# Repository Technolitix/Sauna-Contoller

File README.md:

# Sauna Controller

A project for controlling a sauna using sensors and actuators. This application allows precise management of temperature, humidity, and other parameters to ensure an optimal sauna experience.

---

## Features

- **Temperature Control**: Automatically adjusts the temperature based on predefined settings.
- **Humidity Management**: Integrates humidity sensors for maintaining the perfect sauna environment.
- **Scheduling**: Enables the sauna to operate at predefined times.
- **Fallback Mode**: Ensures stable operation even during connectivity issues.

---

## Configuration Overview

The main configuration file is `sauna1.yaml`. It contains all the necessary settings for operating the sauna controller. Sensitive data such as passwords and API keys are managed through references (`!secret`) in a separate file, such as `secrets.yaml`.

Example of a reference in the YAML file:
```yaml
wifi:
  ssid: !secret wifi_ssid_sauna
  password: !secret wifi_password_sauna
```

### Note
The `secrets.yaml` file is not included in this repository. It should contain sensitive data and remain private.

---

## Directory Structure

- **`config/`**: Contains main configuration files like `sauna1.yaml`.
- **`pictures/`**: Contains images for documentation and illustration.
- **`scripts/`**: Scripts supporting sauna control.
- **`logs/`**: Log files for debugging and tracking.

---

## Installation and Usage

### Prerequisites

- A device capable of managing the controller (e.g., Raspberry Pi, ESP32).
- Sensors and actuators compatible with the sauna setup.

### Steps

1. **Clone the repository**:
   ```bash
   git clone https://github.com/Technolitix/Sauna-Controller.git
   ```
2. **Adjust the configuration file**:
   Edit `sauna1.yaml` to suit your sauna's specific requirements.
3. **Configure secrets**:
   Create a `secrets.yaml` file and add sensitive data:
   ```yaml
   wifi_ssid_sauna: "YourWiFiName"
   wifi_password_sauna: "YourWiFiPassword"
   ```
4. **Deploy and start**:
   Upload the configuration to your device and start the controller.

---

## Security

- The `secrets.yaml` file should never be included in the repository.
- Always ensure sensitive data is stored externally and securely.

---

## Contact

If you have any questions or issues, feel free to open an [Issue](https://github.com/Technolitix/Sauna-Controller/issues).

---

## License

This project is licensed under the [MIT License](LICENSE).

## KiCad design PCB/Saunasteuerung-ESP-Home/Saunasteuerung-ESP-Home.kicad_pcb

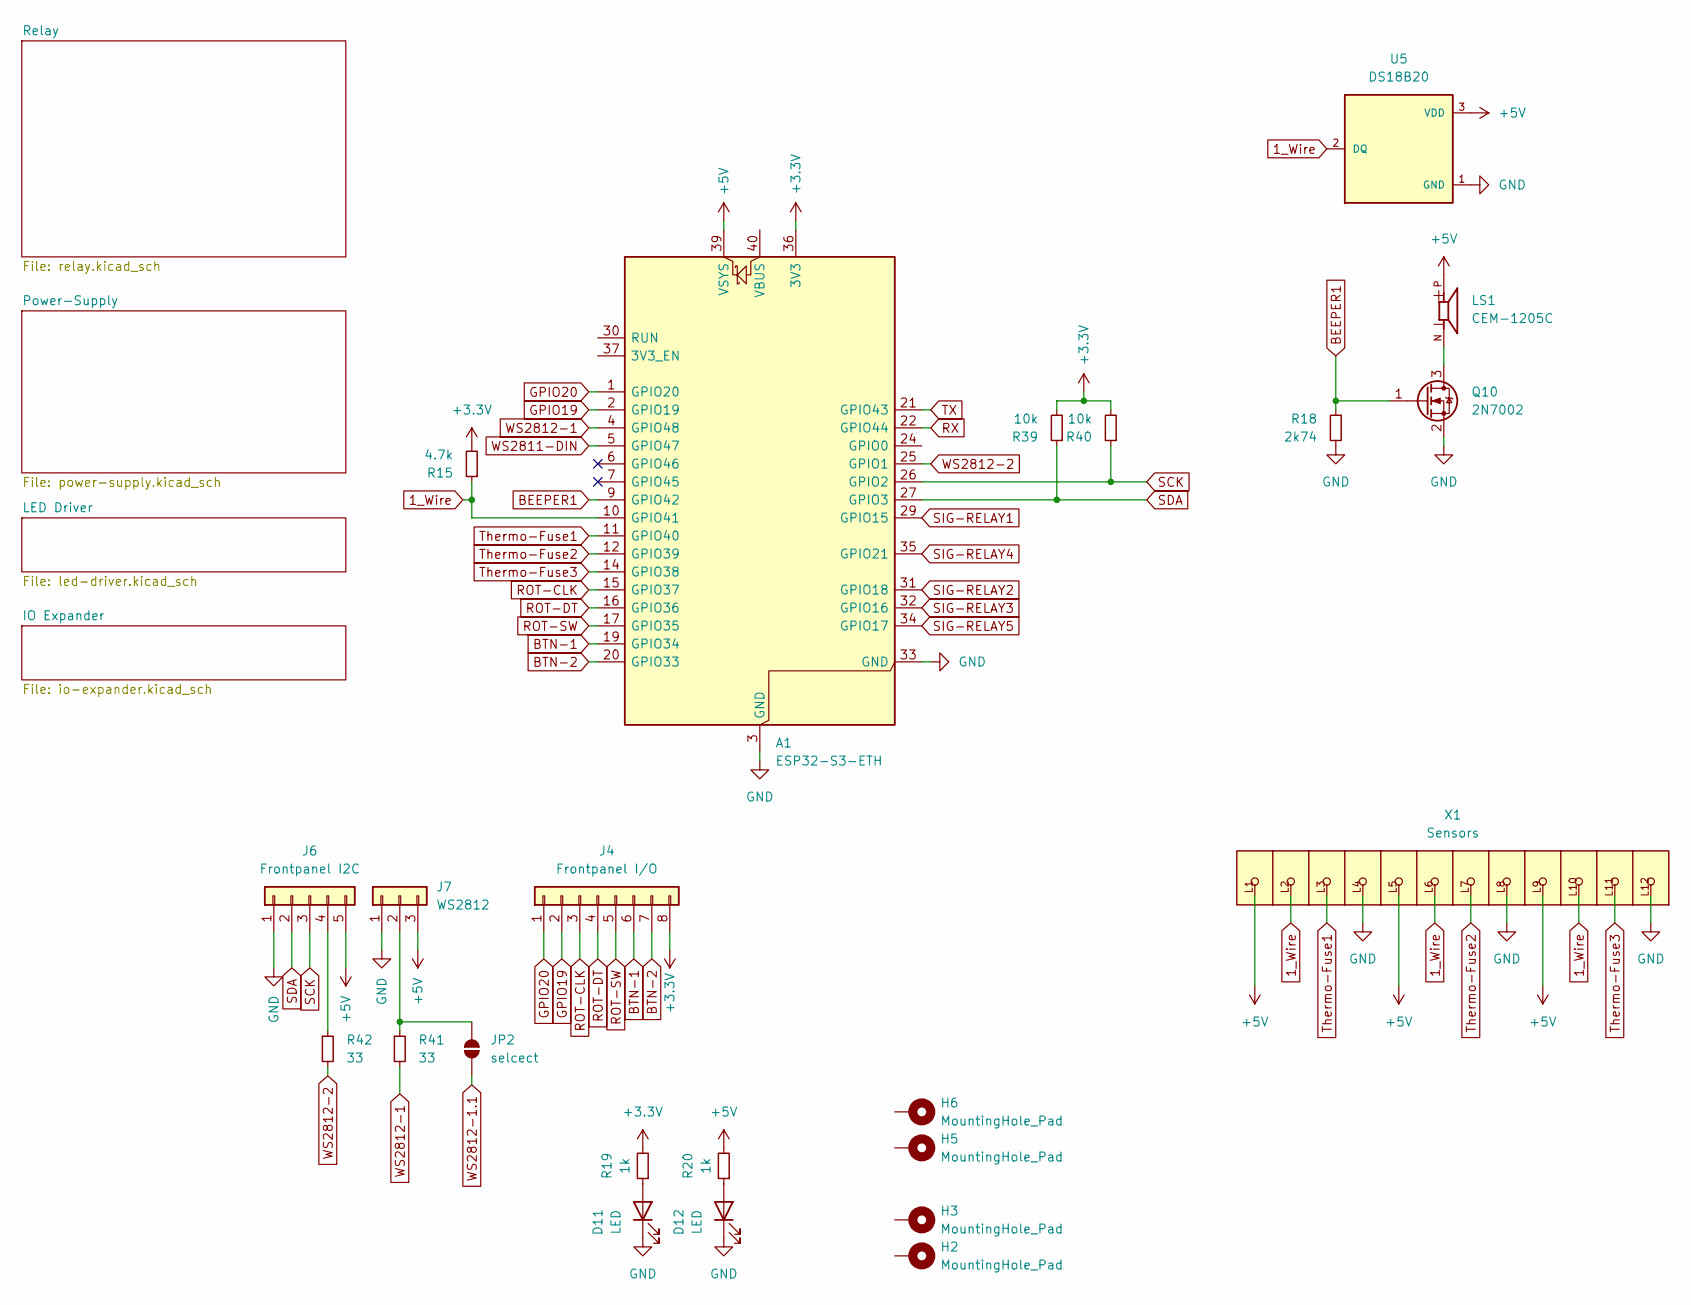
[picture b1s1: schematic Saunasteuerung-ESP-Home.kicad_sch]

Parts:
A1: ESP32-S3-ETH
D11, D12: LED; LED_0603_1608Metric
H2, H3, H5, H6: MountingHole_Pad; MountingHole_3.2mm_M3_DIN965_Pad_TopBottom
J4: Frontpanel I/O; JST_XH_B8B-XH-A_1x08_P2.50mm_Vertical
J6: Frontpanel I2C; JST_XH_B5B-XH-A_1x05_P2.50mm_Vertical
J7: WS2812; JST_XH_B3B-XH-A_1x03_P2.50mm_Vertical
JP2: selcect; SolderJumper-2_P1.3mm_Open_TrianglePad1.0x1.5mm
LS1: CEM-1205C; CEM-1205C_CUI_CEM-1205C
Q10: 2N7002; SOT-23
R15: 4.7k; R_0603_1608Metric
R18: 2k74; R_0603_1608Metric
R19, R20: 1k; R_0603_1608Metric
R39, R40: 10k; R_0603_1608Metric
R41, R42: 33; R_0603_1608Metric
U5: DS18B20; TO-92L; PARTREV 5
X1: Sensors; 250-212_P-250-212

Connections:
1_Wire: A1.10 (GPIO41), R15.1, U5.2 (DQ), X1.L2, X1.L6, X1.L10
+3.3V: A1.36 (3V3), J4.8, R15.2, R19.2, R39.2, R40.2
+5V: A1.39 (VSYS), J6.5, J7.3, LS1.P, R20.2, U5.3 (VDD), X1.L1, X1.L5, X1.L9; also elsewhere on the board
BEEPER1: A1.9 (GPIO42), Q10.1 (G), R18.1
BTN-1: A1.19 (GPIO34), J4.6
BTN-2: A1.20 (GPIO33), J4.7
GND: A1.3 (GND), A1.8 (GND), A1.13 (GND), A1.18 (GND), A1.23 (GND), A1.28 (GND), A1.33 (GND), A1.38 (GND), D11.1 (K), D12.1 (K), J6.1, J7.1, Q10.2 (S), R18.2, U5.1 (GND), X1.L4, X1.L8, X1.L12; also elsewhere on the board
GPIO19: A1.2 (GPIO19), J4.2
GPIO20: A1.1 (GPIO20), J4.1
unnamed: D11.2 (A), R19.1
unnamed: D12.2 (A), R20.1
unnamed: J6.4, R42.1
unnamed: J7.2, JP2.2 (B), R41.1
unnamed: LS1.N, Q10.3 (D)
ROT-CLK: A1.15 (GPIO37), J4.3
ROT-DT: A1.16 (GPIO36), J4.4
ROT-SW: A1.17 (GPIO35), J4.5
RX: A1.22 (GPIO44)
SCK: A1.26 (GPIO2), J6.3, R40.1
SDA: A1.27 (GPIO3), J6.2, R39.1
SIG-RELAY1: A1.29 (GPIO15); also elsewhere on the board
SIG-RELAY2: A1.31 (GPIO18); also elsewhere on the board
SIG-RELAY3: A1.32 (GPIO16); also elsewhere on the board
SIG-RELAY4: A1.35 (GPIO21); also elsewhere on the board
SIG-RELAY5: A1.34 (GPIO17); also elsewhere on the board
TX: A1.21 (GPIO43)
Thermo-Fuse1: A1.11 (GPIO40), X1.L3
Thermo-Fuse2: A1.12 (GPIO39), X1.L7
Thermo-Fuse3: A1.14 (GPIO38), X1.L11
WS2811-DIN: A1.5 (GPIO47); also elsewhere on the board
WS2812-1: A1.4 (GPIO48), R41.2
WS2812-1.1: JP2.1 (A); also elsewhere on the board
WS2812-2: A1.25 (GPIO1), R42.2

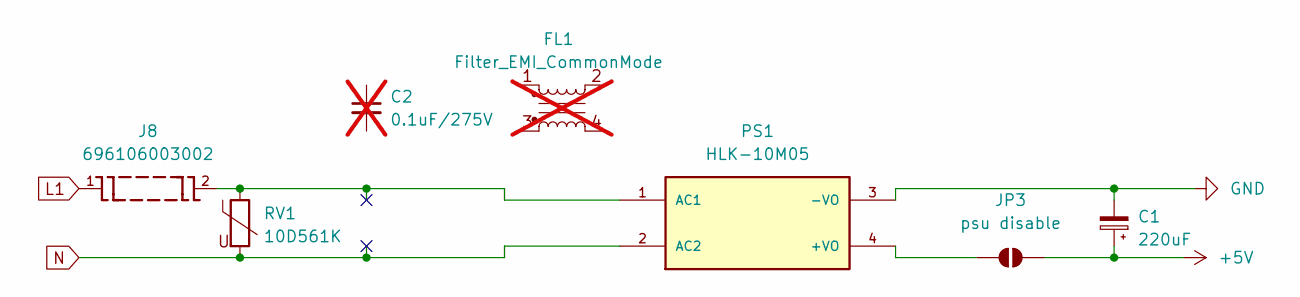
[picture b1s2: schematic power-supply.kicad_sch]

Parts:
C1: 220uF; CP_Elec_6.3x3.9
C2: 0.1uF/275V; not fitted
FL1: Filter_EMI_CommonMode; L_CommonMode_PulseElectronics_PH9455x105NL_1; not fitted
J8: 696106003002; 696106003002_696106003002; PART-NUMBER 696106003002
JP3: psu disable; SolderJumper-2_P1.3mm_Bridged_Pad1.0x1.5mm
PS1: HLK-10M05; HLK-10M05_CONV_HLK-10M05; PARTREV V1.8
RV1: 10D561K; RV_Disc_D7mm_W3.4mm_P5mm

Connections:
+5V: C1.1, JP3.2 (B); also elsewhere on the board
GND: C1.2, PS1.3 (-VO); also elsewhere on the board
L1: J8.1; also elsewhere on the board
N: PS1.2 (AC2), RV1.2; also elsewhere on the board
unnamed: JP3.1 (A), PS1.4 (+VO)

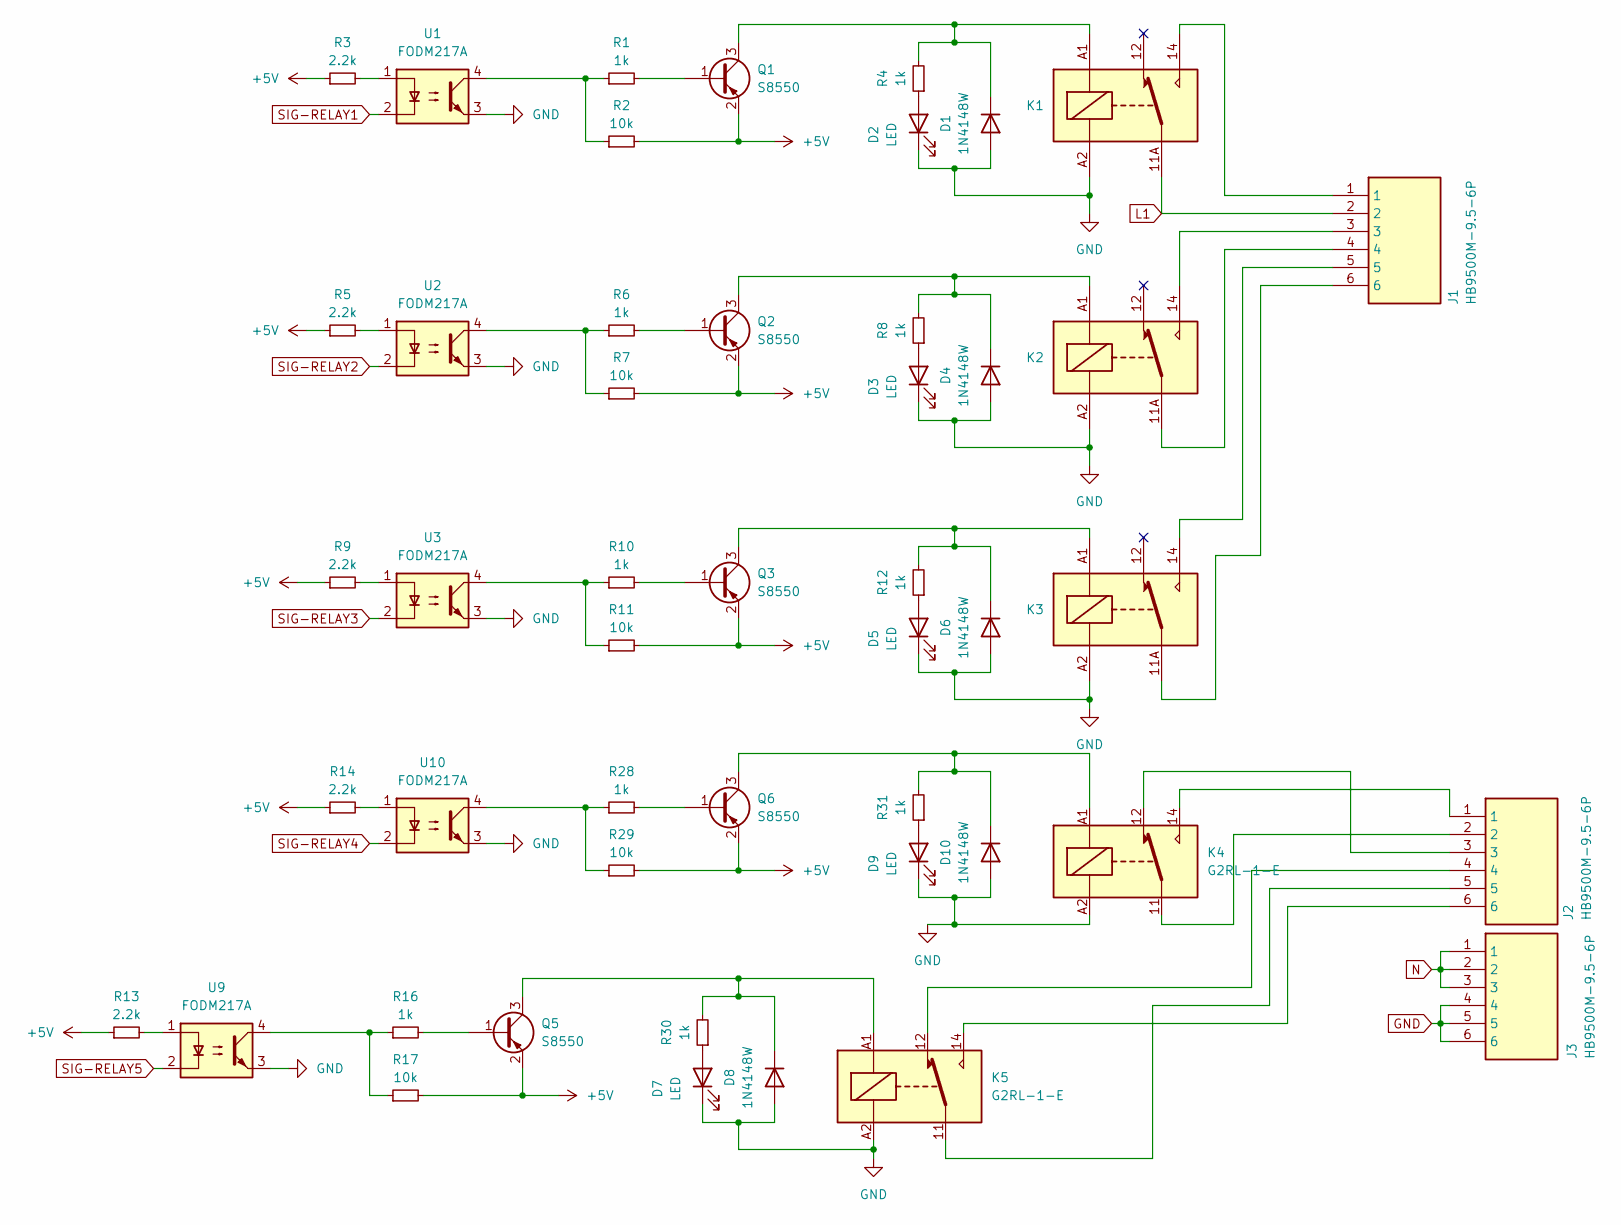
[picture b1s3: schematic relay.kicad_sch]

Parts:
D1, D4, D6, D8, D10: 1N4148W; D_SOD-123
D2, D3, D5, D7, D9: LED; LED_0603_1608Metric
J1, J2, J3: HB9500M-9.5-6P; HB9500M956P; Manufacturer_Part_Number HB9500M-9.5-6P
K1, K2, K3: RAYEX-L90; Relay_SPDT_RAYEX-L90
K4, K5: G2RL-1-E; Relay_SPDT_Omron_G2RL-1-E
Q1, Q2, Q3, Q5, Q6: S8550; SOT-23
R1, R4, R6, R8, R10, R12, R16, R28, R30, R31: 1k; R_0603_1608Metric
R2, R7, R11, R17, R29: 10k; R_0603_1608Metric
R3, R5, R9, R13, R14: 2.2k; R_0603_1608Metric
U1, U2, U3, U9, U10: FODM217A; SOP-4_4.4x2.6mm_P1.27mm

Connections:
+5V: Q1.2 (E), Q2.2 (E), Q3.2 (E), Q5.2 (E), Q6.2 (E), R2.2, R3.1, R5.1, R7.2, R9.1, R11.2, R13.1, R14.1, R17.2, R29.2; also elsewhere on the board
GND: D1.2 (A), D2.1 (K), D3.1 (K), D4.2 (A), D5.1 (K), D6.2 (A), D7.1 (K), D8.2 (A), D9.1 (K), D10.2 (A), J3.4, J3.5, J3.6, K1.A2, K2.A2, K3.A2, K4.A2, K5.A2, U1.3, U2.3, U3.3, U9.3, U10.3; also elsewhere on the board
L1: J1.2, K1.11A, K1.11B; also elsewhere on the board
N: J3.1, J3.2, J3.3; also elsewhere on the board
unnamed: D1.1 (K), K1.A1, Q1.3 (C), R4.2
unnamed: D2.2 (A), R4.1
unnamed: D3.2 (A), R8.1
unnamed: D4.1 (K), K2.A1, Q2.3 (C), R8.2
unnamed: D5.2 (A), R12.1
unnamed: D6.1 (K), K3.A1, Q3.3 (C), R12.2
unnamed: D7.2 (A), R30.1
unnamed: D8.1 (K), K5.A1, Q5.3 (C), R30.2
unnamed: D9.2 (A), R31.1
unnamed: D10.1 (K), K4.A1, Q6.3 (C), R31.2
unnamed: J1.1, K1.14
unnamed: J1.3, K2.14
unnamed: J1.4, K2.11A, K2.11B
unnamed: J1.5, K3.14
unnamed: J1.6, K3.11A, K3.11B
unnamed: J2.1, K4.14
unnamed: J2.2, K4.11
unnamed: J2.3, K4.12
unnamed: J2.4, K5.12
unnamed: J2.5, K5.11
unnamed: J2.6, K5.14
unnamed: Q1.1 (B), R1.2
unnamed: Q2.1 (B), R6.2
unnamed: Q3.1 (B), R10.2
unnamed: Q5.1 (B), R16.2
unnamed: Q6.1 (B), R28.2
unnamed: R1.1, R2.1, U1.4
unnamed: R3.2, U1.1
unnamed: R5.2, U2.1
unnamed: R6.1, R7.1, U2.4
unnamed: R9.2, U3.1
unnamed: R10.1, R11.1, U3.4
unnamed: R13.2, U9.1
unnamed: R14.2, U10.1
unnamed: R16.1, R17.1, U9.4
unnamed: R28.1, R29.1, U10.4
SIG-RELAY1: U1.2; also elsewhere on the board
SIG-RELAY2: U2.2; also elsewhere on the board
SIG-RELAY3: U3.2; also elsewhere on the board
SIG-RELAY4: U10.2; also elsewhere on the board
SIG-RELAY5: U9.2; also elsewhere on the board

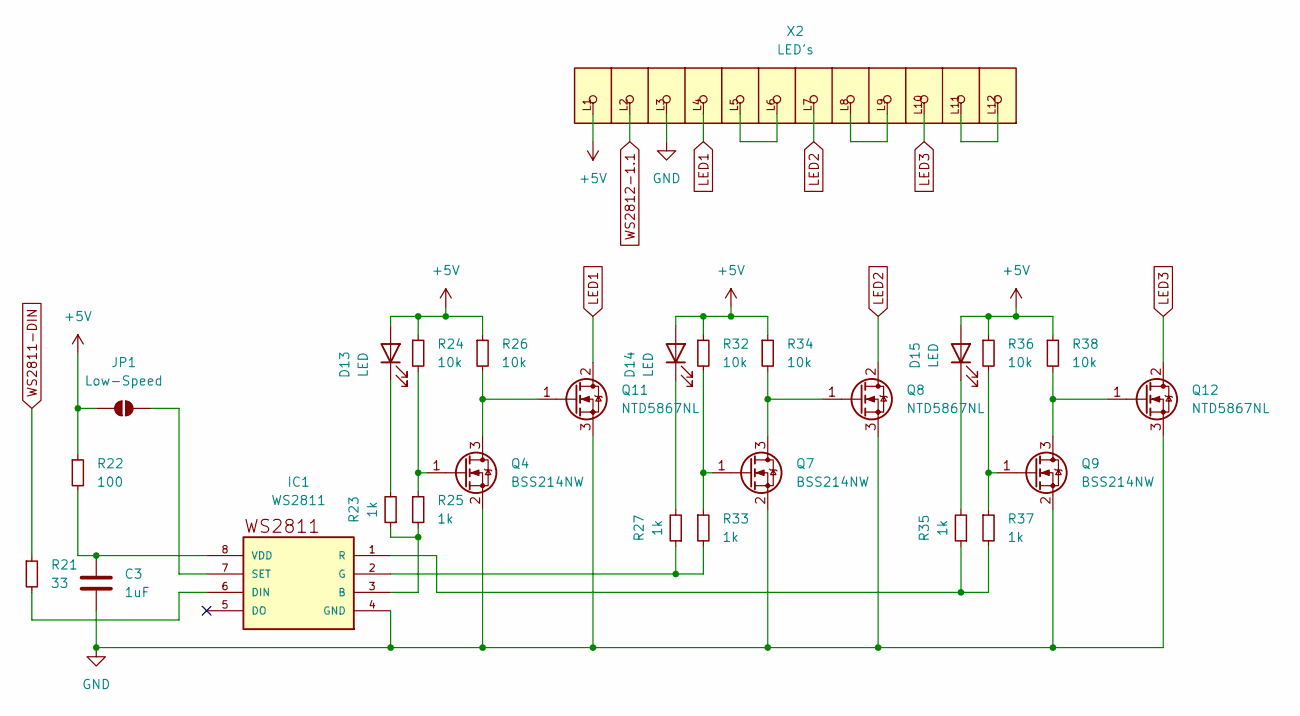
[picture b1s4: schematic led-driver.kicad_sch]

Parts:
C3: 1uF; C_0603_1608Metric
D13, D14, D15: LED; LED_0603_1608Metric
IC1: WS2811; SO08-SKINNYPADS
JP1: Low-Speed; SolderJumper-2_P1.3mm_Open_TrianglePad1.0x1.5mm
Q4, Q7, Q9: BSS214NW; SOT-323_SC-70
Q8, Q11, Q12: NTD5867NL; TO-252-2
R21: 33; R_0603_1608Metric
R22: 100; R_0603_1608Metric
R23, R25, R27, R33, R35, R37: 1k; R_0603_1608Metric
R24, R26, R32, R34, R36, R38: 10k; R_0603_1608Metric
X2: LED's; 250-212_P-250-212

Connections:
+5V: D13.2 (A), D14.2 (A), D15.2 (A), JP1.2 (B), R22.1, R24.1, R26.1, R32.1, R34.1, R36.1, R38.1, X2.L1; also elsewhere on the board
GND: C3.2, IC1.4 (GND), Q4.2 (S), Q7.2 (S), Q8.3 (S), Q9.2 (S), Q11.3 (S), Q12.3 (S), X2.L3; also elsewhere on the board
LED1: Q11.2 (D), X2.L4
LED2: Q8.2 (D), X2.L7
LED3: Q12.2 (D), X2.L10
unnamed: D13.1 (K), R23.2
unnamed: D14.1 (K), R27.2
unnamed: D15.1 (K), R35.2
unnamed: IC1.3 (B), R23.1, R25.2
unnamed: IC1.6 (DIN), R21.2
unnamed: IC1.2 (G), R27.1, R33.2
unnamed: IC1.1 (R), R35.1, R37.2
unnamed: IC1.7 (SET), JP1.1 (A)
unnamed: C3.1, IC1.8 (VDD), R22.2
unnamed: Q4.1 (G), R24.2, R25.1
unnamed: Q7.3 (D), Q8.1 (G), R34.2
unnamed: Q7.1 (G), R32.2, R33.1
unnamed: Q9.1 (G), R36.2, R37.1
unnamed: Q4.3 (D), Q11.1 (G), R26.2
unnamed: Q9.3 (D), Q12.1 (G), R38.2
unnamed: X2.L5, X2.L6
unnamed: X2.L8, X2.L9
unnamed: X2.L11, X2.L12
WS2811-DIN: R21.1; also elsewhere on the board
WS2812-1.1: X2.L2; also elsewhere on the board

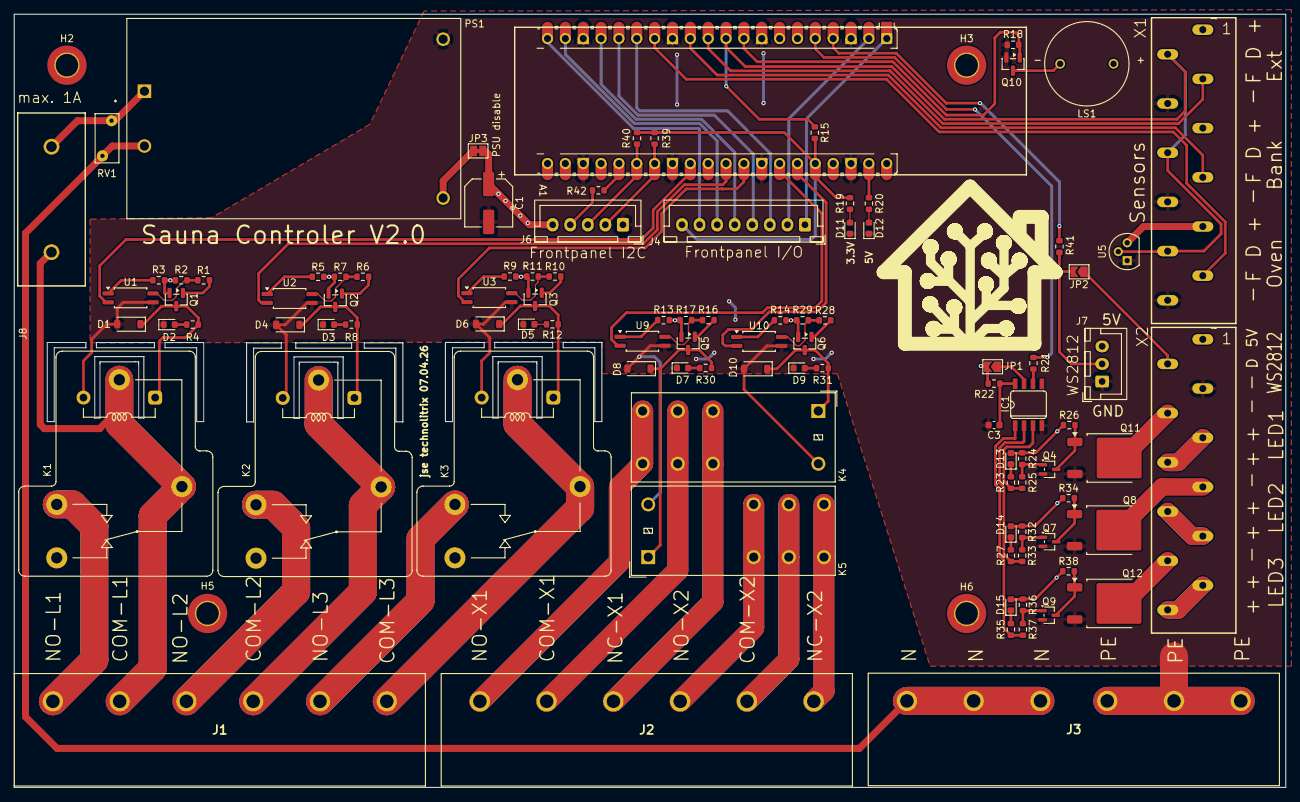
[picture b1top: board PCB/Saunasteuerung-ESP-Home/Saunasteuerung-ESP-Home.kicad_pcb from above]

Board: 2 copper layers, 180.9 x 110.0 mm, 103 parts (0 on the bottom side), 91 nets.

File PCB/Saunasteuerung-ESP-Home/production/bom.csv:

Designator,Footprint,Quantity,Value,LCSC Part #
A1,ESP32-S3-ETH,1,ESP32-S3-ETH,
C1,CP_Elec_6.3x3.9,1,220uF,
C3,0603,1,1uF,
"D1, D10, D4, D6, D8",D_SOD-123,5,1N4148W,
"D11, D12, D13, D14, D15, D2, D3, D5, D7, D9",0603,10,LED,
IC1,SO08-SKINNYPADS,1,WS2811,
"J1, J2, J3",HB9500M956P,3,HB9500M-9.5-6P,
J4,JST_XH_B8B-XH-A_1x08_P2.50mm_Vertical,1,Frontpanel I/O,
J6,JST_XH_B5B-XH-A_1x05_P2.50mm_Vertical,1,Frontpanel I2C,
J7,JST_XH_B3B-XH-A_1x03_P2.50mm_Vertical,1,WS2812,
J8,696106003002_696106003002,1,696106003002,
"K1, K2, K3",Relay_SPDT_RAYEX-L90,3,RAYEX-L90,
"K4, K5",Relay_SPDT_Omron_G2RL-1-E,2,G2RL-1-E,
LS1,CEM-1205C_CUI_CEM-1205C,1,CEM-1205C,
PS1,HLK-10M05_CONV_HLK-10M05,1,HLK-10M05,
"Q1, Q2, Q3, Q5, Q6",SOT-23,5,S8550,
Q10,SOT-23,1,2N7002,
"Q11, Q12, Q8",TO-252-2,3,NTD5867NL,
"Q4, Q7, Q9",SOT-323_SC-70,3,BSS214NW,
"R1, R10, R12, R16, R19, R20, R23, R25, R27, R28, R30, R31, R33, R35, R37, R4, R6, R8",0603,18,1k,
"R11, R17, R2, R24, R26, R29, R32, R34, R36, R38, R39, R40, R7",0603,13,10k,
"R13, R14, R3, R5, R9",0603,5,2.2k,
R15,0603,1,4.7k,
R18,0603,1,2k74,
"R21, R41, R42",0603,3,33,
R22,0603,1,100,
RV1,RV_Disc_D7mm_W3.4mm_P5mm,1,10D561K,
"U1, U10, U2, U3, U9",SOP-4_4.4x2.6mm_P1.27mm,5,FODM217A,
U5,TO-92L,1,DS18B20,
X1,250-212_P-250-212,1,Sensors,
X2,250-212_P-250-212,1,LED's,

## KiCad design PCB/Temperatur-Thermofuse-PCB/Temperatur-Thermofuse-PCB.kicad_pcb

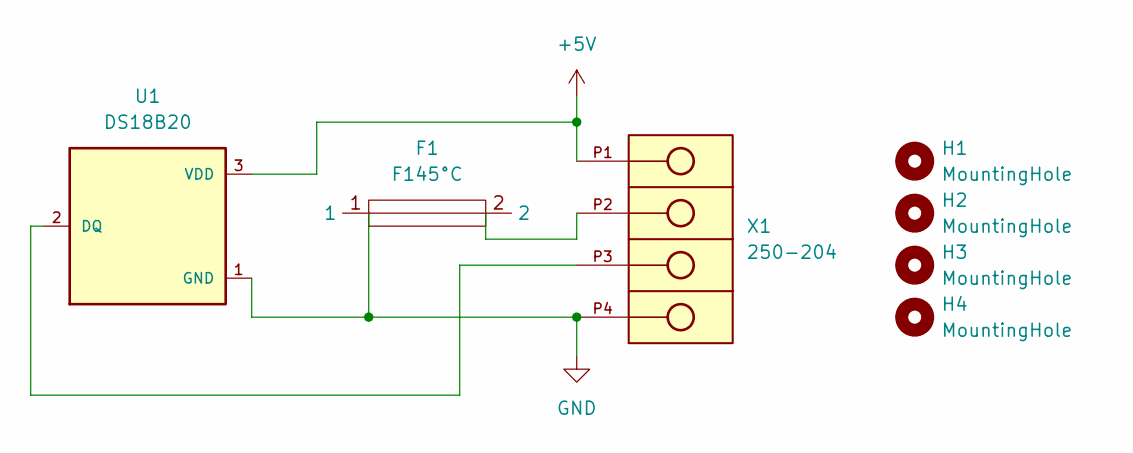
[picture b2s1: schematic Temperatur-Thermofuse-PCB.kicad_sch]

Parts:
F1: F145°C; THERMALFUSE
H1, H2, H3, H4: MountingHole; MountingHole_3.2mm_M3
U1: DS18B20; DS18B20_TO-92-TO92127P495H2044-3; PARTREV 5
X1: 250-204; 250-204_WAGO_250-204

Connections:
+5V: U1.3 (VDD), X1.P1
GND: F1.1, U1.1 (GND), X1.P4
unnamed: F1.2, X1.P2
unnamed: U1.2 (DQ), X1.P3

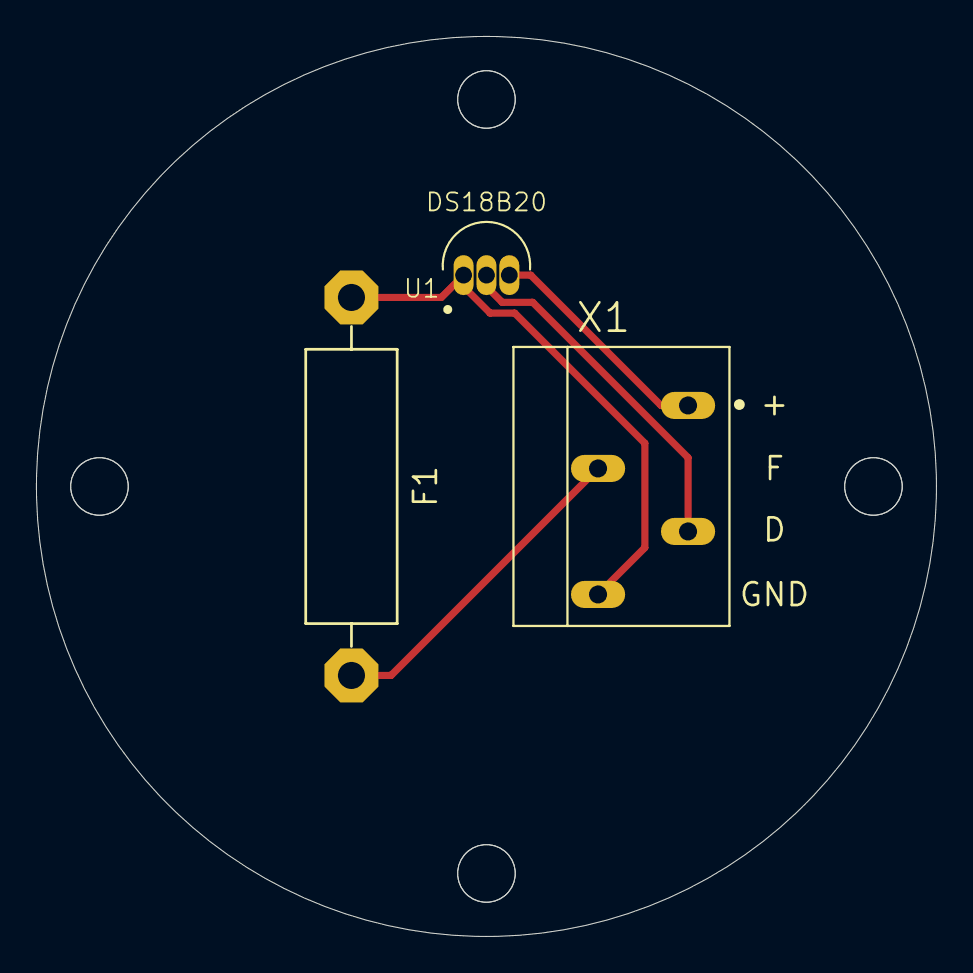
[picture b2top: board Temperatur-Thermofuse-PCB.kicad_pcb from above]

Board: 2 copper layers, 50.0 x 50.0 mm, 7 parts (0 on the bottom side), 4 nets.

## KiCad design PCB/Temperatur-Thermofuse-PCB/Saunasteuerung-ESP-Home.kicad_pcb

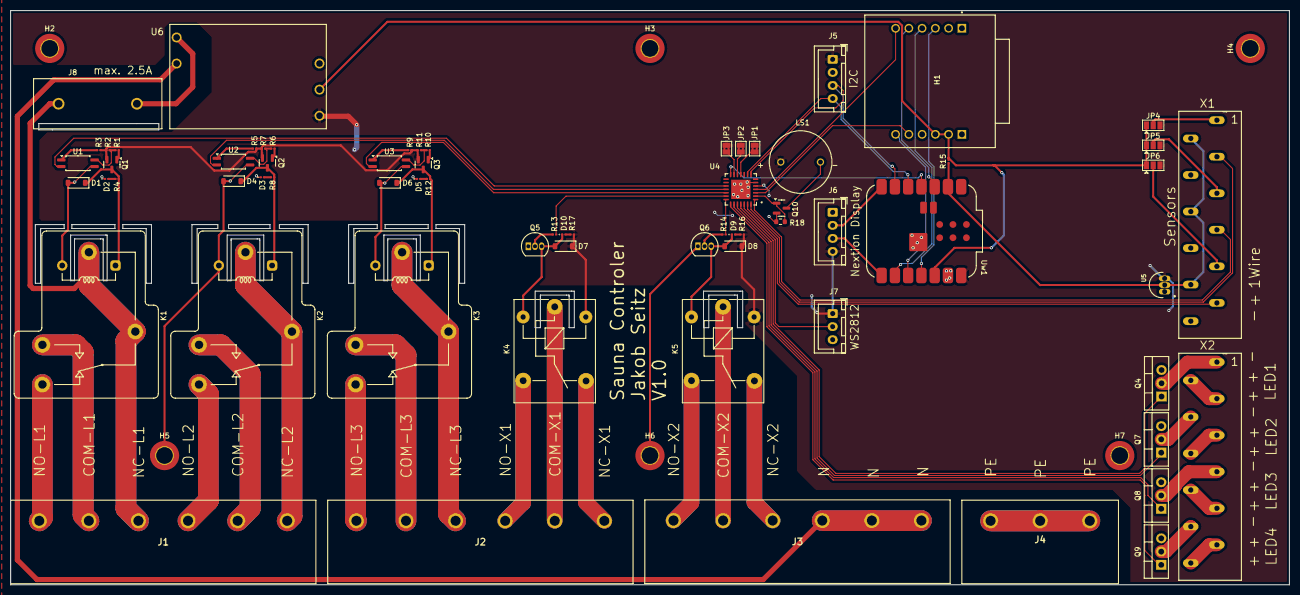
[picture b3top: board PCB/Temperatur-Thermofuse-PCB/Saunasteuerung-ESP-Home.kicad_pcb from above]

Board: 2 copper layers, 245.0 x 110.0 mm, 74 parts (0 on the bottom side), 83 nets.

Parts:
D1, D4, D6, D7, D8: 1N4148W; D_SOD-123
D2, D3, D5, D9, D10: LED; LED_0201_0603Metric
H1: WIZ850IO; WIZ850IO_WIZ850IO
H2, H3, H4, H5, H6, H7: MountingHole_Pad; MountingHole_3.2mm_M3_DIN965_Pad_TopBottom
J1, J2, J3: HB9500M-9.5-6P; HB9500M956P
J4: HB9500M-9.5-3P; HB9500M953P
J5: I2C; JST_XH_B4B-XH-A_1x04_P2.50mm_Vertical
J6: Nextion Display; JST_XH_B4B-XH-A_1x04_P2.50mm_Vertical
J7: WS2812; JST_XH_B3B-XH-A_1x03_P2.50mm_Vertical
J8: 696106003002; 696106003002_696106003002
JP1: A0; SolderJumper-2_P1.3mm_Bridged2Bar_Pad1.0x1.5mm
JP2: A1; SolderJumper-2_P1.3mm_Bridged2Bar_Pad1.0x1.5mm
JP3: A2; SolderJumper-2_P1.3mm_Bridged2Bar_Pad1.0x1.5mm
JP4, JP5, JP6: 3.3/5V; SolderJumper-3_P1.3mm_Open_Pad1.0x1.5mm
K1, K2, K3: RAYEX-L90; Relay_SPDT_RAYEX-L90
K4, K5: SANYOU_SRD_Form_C; Relay_SPDT_SANYOU_SRD_Series_Form_C
LS1: CEM-1205C; CEM-1205C_CUI_CEM-1205C
Q1, Q2, Q3: S8550; SOT-23
Q4, Q7, Q8, Q9: IRLZ34N; TO-220-3_Vertical
Q5, Q6: 2N222; TO-92_Inline
Q10: 2N7002; SOT-23
R1, R4, R6, R8, R10, R12, R16, R17: 1k; R_0201_0603Metric
R2, R7, R11: 10k; R_0201_0603Metric
R3, R5, R9, R13, R14: 2.2k; R_0201_0603Metric
R15: 4.7k; R_0201_0603Metric
R18: 2k74; R_0603_1608Metric
U1, U2, U3: FODM217A; SOP-4_4.4x2.6mm_P1.27mm
U4: MCP23017T-E_ML; MCP23017T-E_ML_QFN65P600X600X100-29N
U5: DS18B20; DS18B20_TO-92-TO92127P495H2044-3
U6: 230V-5V-Step-down; 230V-5V-STEPDOWN
Uw1: MOUDLE-SEEEDUINO-XIAO-ESP32C3; MCU_Seeed_ESP32C3
X1: Sensors; 250-212_P-250-212
X2: LED's; 250-212_P-250-212

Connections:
1_Wire: R15.1, U5.2 (DQ), Uw1.2 (PA4_A1_D1), X1.L2, X1.L6, X1.L10
+3.3V: H1.8 (3.3V_1), H1.9 (3.3V_2), JP4.1 (A), JP5.1 (A), JP6.1 (A), R15.2, U6.3.3V, Uw1.12 (3V3)
+5V: D7.1 (K), D8.1 (K), J5.1, J6.4, J7.1, JP1.1 (A), JP2.1 (A), JP3.1 (A), JP4.3 (B), JP5.3 (B), JP6.3 (B), K4.5, K5.5, LS1.P, Q1.2 (E), Q2.2 (E), Q3.2 (E), R2.2, R3.1, R5.1, R7.2, R9.1, R11.2, R16.2, R17.2, U4.5 (VDD), U5.3 (VDD), U6.5V, Uw1.14 (5V)
BEEPER1: Q10.1 (G), R18.1, U4.2 (GPB5)
GND: D1.2 (A), D2.1 (K), D3.1 (K), D4.2 (A), D5.1 (K), D6.2 (A), H1.1 (GND_1), H1.2 (GND_2), H1.7 (GND_3), H2.1, H3.1, H4.1, H5.1, H6.1, H7.1, J5.2, J6.1, J7.3, K1.A2, K2.A2, K3.A2, Q4.3 (S), Q5.1 (E), Q6.1 (E), Q7.3 (S), Q8.3 (S), Q9.3 (S), Q10.2 (S), R18.2, U1.3, U2.3, U3.3, U4.6 (VSS), U4.29 (EP), U5.1 (GND), U6.GND, Uw1.13 (GND), Uw1.15 (P15_TP_GND), X1.L4, X1.L8, X1.L12
INTN: H1.6 (INTN), U4.4 (GPB7)
L1: J1.3, J8.1, K1.11A, K1.11B
LED1: Q4.2 (D), X2.L1
LED2: Q7.2 (D), X2.L4
LED3: Q8.2 (D), X2.L7
LED4: Q9.2 (D), X2.L10
MCP23017_RST: U4.14 (~RESET), Uw1.4 (PA11_A3_D3)
MISO: H1.12 (MISO), Uw1.10 (PA5_A9_D9_MISO)
MOSI: H1.3 (MOSI), Uw1.11 (PA6_A10_D10_MOSI)
N: J3.4, J3.5, J3.6, U6.N
unnamed: D1.1 (K), K1.A1, Q1.3 (C), R4.2
unnamed: D2.2 (A), R4.1
unnamed: D3.2 (A), R8.1
unnamed: D4.1 (K), K2.A1, Q2.3 (C), R8.2
unnamed: D5.2 (A), R12.1
unnamed: D6.1 (K), K3.A1, Q3.3 (C), R12.2
unnamed: D8.2 (A), D9.1 (K), K5.2, Q6.3 (C)
unnamed: D9.2 (A), R16.1
unnamed: D10.2 (A), R17.1
unnamed: D7.2 (A), D10.1 (K), K4.2, Q5.3 (C)
unnamed: J1.1, K1.12
unnamed: J1.2, K1.14
unnamed: J1.4, K2.12
unnamed: J1.5, K2.14
unnamed: J1.6, K2.11A, K2.11B
unnamed: J2.1, K3.12
unnamed: J2.2, K3.14
unnamed: J2.3, K3.11A, K3.11B
unnamed: J2.4, K4.3
unnamed: J2.5, K4.1
unnamed: J2.6, K4.4
unnamed: J3.1, K5.3
unnamed: J3.2, K5.1
unnamed: J3.3, K5.4
unnamed: J8.2, U6.L
unnamed: JP1.2 (B), U4.11 (A0)
unnamed: JP2.2 (B), U4.12 (A1)
unnamed: JP3.2 (B), U4.13 (A2)
unnamed: JP4.2 (C), X1.L1
unnamed: JP5.2 (C), X1.L5
unnamed: JP6.2 (C), X1.L9
unnamed: Q1.1 (B), R1.2
unnamed: Q2.1 (B), R6.2
unnamed: Q3.1 (B), R10.2
unnamed: Q5.2 (B), R13.2
unnamed: Q6.2 (B), R14.2
unnamed: LS1.N, Q10.3 (D)
unnamed: R1.1, R2.1, U1.4
unnamed: R3.2, U1.1
unnamed: R5.2, U2.1
unnamed: R6.1, R7.1, U2.4
unnamed: R9.2, U3.1
unnamed: R10.1, R11.1, U3.4
unnamed: X2.L2, X2.L3
unnamed: X2.L5, X2.L6
unnamed: X2.L8, X2.L9
unnamed: X2.L11, X2.L12
PE: J4.1, J4.2, J4.3
RESTN: H1.11 (RSTN), U4.3 (GPB6)
RX: J6.3, Uw1.8 (PB09_A7_D7_RX)
SCK: J5.3, U4.8 (SCK), Uw1.6 (PA9_A5_D5_SCL)
SCLK: H1.4 (SCLK), Uw1.9 (PA7_A8_D8_SCK)
SCNN: H1.5 (SCNN), Uw1.3 (PA10_A2_D2)
SDA: J5.4, U4.9 (SDA), Uw1.5 (PA8_A4_D4_SDA)
SIG-LED1: Q4.1 (G), U4.25 (GPB0)
SIG-LED2: Q7.1 (G), U4.24 (GPA7)
SIG-LED3: Q8.1 (G), U4.23 (GPA6)
SIG-LED4: Q9.1 (G), U4.22 (GPA5)
SIG-RELAY1: U1.2, U4.17 (GPA0)
SIG-RELAY2: U2.2, U4.18 (GPA1)
SIG-RELAY3: U3.2, U4.19 (GPA2)
SIG-RELAY4: R13.1, U4.20 (GPA3)
SIG-RELAY5: R14.1, U4.21 (GPA4)
TX: J6.2, Uw1.7 (PB08_A6_D6_TX)
Thermo-Fuse1: U4.28 (GPB3), X1.L3
Thermo-Fuse2: U4.1 (GPB4), X1.L7
Thermo-Fuse3: U4.27 (GPB2), X1.L11
WS2812: J7.2, U4.26 (GPB1)

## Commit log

2024-11-23 Inital Commit
2024-11-23 Update Picture
2025-03-09 Added AD5593
2026-03-25 removed old pcb files
2026-04-06 V2.0 push
2026-04-06 rm backups
